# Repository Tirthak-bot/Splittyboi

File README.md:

# Splittyboi
A Split keyboard with low profile switches, Coded with KMK Firmware.

Making this because i want to try a split keeb :3

Using this is pretty straight forward obviously blehh, just connect it to the computer, flash the firmware once and it should just work like a regular keeb moving forward :)

# Schematic
This is the schematic for a single side, both sides are made identically.

# Layout
The layout was designed on https://www.keyboard-layout-editor.com/, The firmware hasn't yet been edited to match this layout and is currently sitting with placeholders.

# PCB
The PCB was designed in Kicad. The matrix wasn't properly aligned to make the look of the PCB More intresting, it will be coded in properly afterwards (Once I make it IRL).

# Case
The case was designed in Fusion. Both sides of the case are based on the same footprint but once it is extruded in the positive axis and once in negetive axis to get a identical case accommodating both right and left sides.

You just drop the pcb in place :) and for the both halfs of the case, they join using magnets!

The magnets are glue and drop, not press fit! So the thin walls around the magnet holes won't cause any problems!

# Firmware
As mentioned above, the firmware is written in python using the KMK Libraries. It will be pushed to the microcontroller using circuit python.

# BOM
|SR.NO|ITEMS|QUANTITY|UNIT PRICE|TOTAL PRICE|URL|
|-----|-----|--------|-----------|-----------|---|
|1|PCB (From JLCPCB)|5 (Minimun)|$10 (Including Shipping)|$50|In my Cart|
|2|Seeed XIAO nRF52840|2 (One for each side)|$12.50 (Including Shipping)|$25|https://robocraze.com/products/seeed-studio-xiao-nrf52840-development-board-supports-bluetooth-5-0|
|3|Gateron LP 2.0 Switches|70|$0.185 (Including Shipping)|$13|https://meckeys.com/shop/accessories/keyboard-accessories/key-switches/gateron-low-profile-2-0-mechanical-switch-3pin/|
|4|Blank DSA Keycaps 1U|70|$0.207 (Including Shipping)|$14.5|https://meckeys.com/shop/accessories/keyboard-accessories/keycaps/blank-dsa-keycaps-1u/|
|5|3.7V LiPo Batteries|2 (One for each side)|$1.615 (Including Shipping)|$3.23|https://quartzcomponents.com/products/3-7v-1000mah-li-po-rechargeable-battery|
|6|1N4148WS T4 Switching Diode|70|$0.025 (Including Shipping)|$1.78|https://quartzcomponents.com/collections/smd-diodes/products/1n4148ws-t4-switching-diode-sod-123-smd-package|
|7|3D Prints|4 Files|idk|idk|Self printed|
|8|Magnets|14|$0|$0|Self sourced|
|Total:|||-|$110||

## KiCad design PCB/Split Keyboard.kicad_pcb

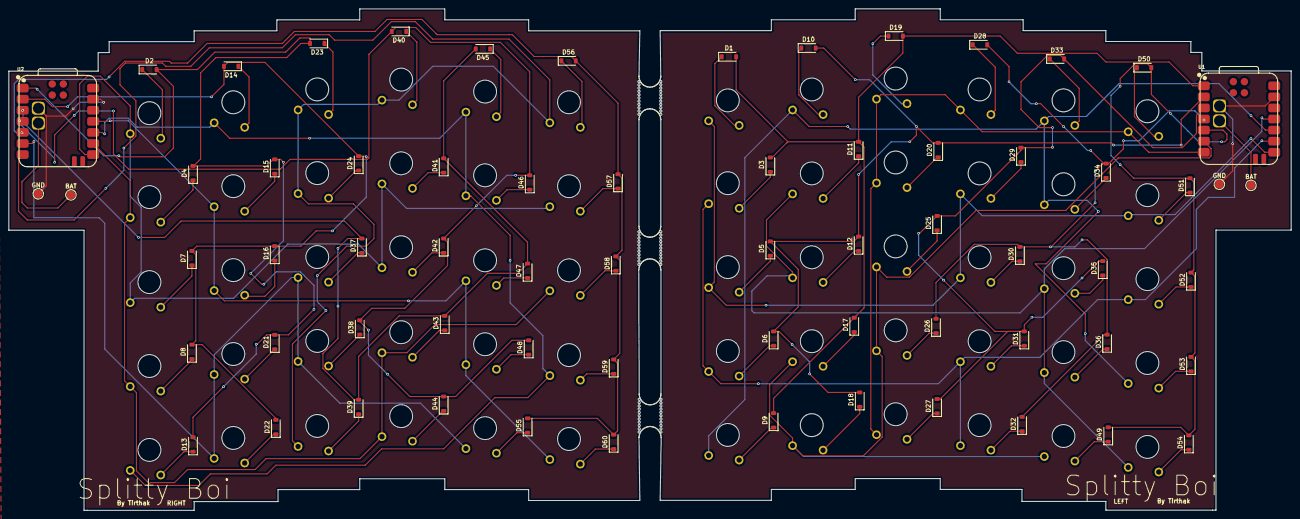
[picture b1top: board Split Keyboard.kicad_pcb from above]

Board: 2 copper layers, 294.2 x 115.0 mm, 129 parts (0 on the bottom side), 74 nets.

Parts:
BAT: BAT; TestPoint_Pad_D2.0mm
BAT#2: BAT; TestPoint_Pad_D2.0mm
D1, D2, D3, D4, D5, D6, D7, D8, D9, D10, D11, D12, D13, D14, D15, D16, D17, D18, D19, D20, D21, D22, D23, D24, D25, D26, D27, D28, D29, D30, D31, D32, D33, D34, D35, D36, D37, D38, D39, D40, D41, D42, D43, D44, D45, D46, D47, D48, D49, D50, D51, D52, D53, D54, D55, D56, D57, D58, D59, D60: D; D_SOD-123
GND: GND; TestPoint_Pad_D2.0mm
GND#2: GND; TestPoint_Pad_D2.0mm
SW1, SW2, SW3, SW4, SW5, SW6, SW7, SW8, SW9, SW10, SW11, SW12, SW13, SW14, SW15, SW16, SW17, SW18, SW19, SW20, SW21, SW22, SW23, SW24, SW25, SW26, SW27, SW28, SW29, SW30, SW31, SW32, SW33, SW34, SW35, SW36, SW37, SW38, SW39, SW40, SW41, SW42, SW43, SW44, SW45, SW46, SW47, SW48, SW49, SW50, SW51, SW52, SW53, SW54, SW55, SW56, SW57, SW58, SW59, SW60: SW_Push; SW_KS33_1u
U1, U2: XIAO-nRF52840-SMD; modified-XIAO-nRF52840-SMD
mouse-bite-5mm-slot, mouse-bite-5mm-slot#2, mouse-bite-5mm-slot#3: VAL**; mouse-bite-5mm-slot

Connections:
COL0: D1.2 (A), D2.2 (A), D3.2 (A), D4.2 (A), D9.2 (A), D11.2 (A), D13.2 (A), D15.2 (A), D17.2 (A), D19.2 (A), D21.2 (A), D23.2 (A), U1.1 (P0.02_A0_D0), U2.1 (P0.02_A0_D0)
COL1: D5.2 (A), D6.2 (A), D7.2 (A), D8.2 (A), D10.2 (A), D12.2 (A), D14.2 (A), D16.2 (A), D18.2 (A), D20.2 (A), D22.2 (A), D24.2 (A), U1.2 (P0.03_A1_D1), U2.2 (P0.03_A1_D1)
COL2: D25.2 (A), D27.2 (A), D29.2 (A), D31.2 (A), D33.2 (A), D35.2 (A), D37.2 (A), D39.2 (A), D41.2 (A), D43.2 (A), D45.2 (A), D47.2 (A), U1.3 (P0.28_A2_D2), U2.3 (P0.28_A2_D2)
COL3: D26.2 (A), D28.2 (A), D30.2 (A), D32.2 (A), D34.2 (A), D36.2 (A), D38.2 (A), D40.2 (A), D42.2 (A), D44.2 (A), D46.2 (A), D48.2 (A), U1.4 (P0.29_A3_D3), U2.4 (P0.29_A3_D3)
COL4: D49.2 (A), D50.2 (A), D51.2 (A), D52.2 (A), D53.2 (A), D54.2 (A), D55.2 (A), D56.2 (A), D57.2 (A), D58.2 (A), D59.2 (A), D60.2 (A), U1.5 (P0.04_A4_D4_SDA), U2.5 (P0.04_A4_D4_SDA)
GND: GND.1, GND#2.1, U1.13 (GND), U1.16 (GND), U2.13 (GND), U2.16 (GND)
unnamed: D1.1 (K), SW1.2
unnamed: D2.1 (K), SW2.2
unnamed: D3.1 (K), SW3.2
unnamed: D4.1 (K), SW4.2
unnamed: D5.1 (K), SW5.2
unnamed: D6.1 (K), SW6.2
unnamed: D7.1 (K), SW7.2
unnamed: D8.1 (K), SW8.2
unnamed: D9.1 (K), SW9.2
unnamed: D10.1 (K), SW10.2
unnamed: D11.1 (K), SW11.2
unnamed: D12.1 (K), SW12.2
unnamed: D13.1 (K), SW13.2
unnamed: D14.1 (K), SW14.2
unnamed: D15.1 (K), SW15.2
unnamed: D16.1 (K), SW16.2
unnamed: D17.1 (K), SW17.2
unnamed: D18.1 (K), SW18.2
unnamed: D19.1 (K), SW19.2
unnamed: D20.1 (K), SW20.2
unnamed: D21.1 (K), SW21.2
unnamed: D22.1 (K), SW22.2
unnamed: D23.1 (K), SW23.2
unnamed: D24.1 (K), SW24.2
unnamed: D25.1 (K), SW25.2
unnamed: D26.1 (K), SW26.2
unnamed: D27.1 (K), SW27.2
unnamed: D28.1 (K), SW28.2
unnamed: D29.1 (K), SW29.2
unnamed: D30.1 (K), SW30.2
unnamed: D31.1 (K), SW31.2
unnamed: D32.1 (K), SW32.2
unnamed: D33.1 (K), SW33.2
unnamed: D34.1 (K), SW34.2
unnamed: D35.1 (K), SW35.2
unnamed: D36.1 (K), SW36.2
unnamed: D37.1 (K), SW37.2
unnamed: D38.1 (K), SW38.2
unnamed: D39.1 (K), SW39.2
unnamed: D40.1 (K), SW40.2
unnamed: D41.1 (K), SW41.2
unnamed: D42.1 (K), SW42.2
unnamed: D43.1 (K), SW43.2
unnamed: D44.1 (K), SW44.2
unnamed: D45.1 (K), SW45.2
unnamed: D46.1 (K), SW46.2
unnamed: D47.1 (K), SW47.2
unnamed: D48.1 (K), SW48.2
unnamed: D49.1 (K), SW49.2
unnamed: D50.1 (K), SW50.2
unnamed: D51.1 (K), SW51.2
unnamed: D52.1 (K), SW52.2
unnamed: D53.1 (K), SW53.2
unnamed: D54.1 (K), SW54.2
unnamed: D55.1 (K), SW55.2
unnamed: D56.1 (K), SW56.2
unnamed: D57.1 (K), SW57.2
unnamed: D58.1 (K), SW58.2
unnamed: D59.1 (K), SW59.2
unnamed: D60.1 (K), SW60.2
unnamed: BAT.1, U1.15 (BAT)
unnamed: BAT#2.1, U2.15 (BAT)
ROW0: SW17.1, SW18.1, SW21.1, SW22.1, SW25.1, SW26.1, SW37.1, SW38.1, SW49.1, SW55.1, U1.6 (P0.05_A5_D5_SCL), U2.6 (P0.05_A5_D5_SCL)
ROW1: SW19.1, SW20.1, SW23.1, SW24.1, SW27.1, SW28.1, SW39.1, SW40.1, SW50.1, SW56.1, U1.7 (P1.11_D6_TX), U2.7 (P1.11_D6_TX)
ROW2: SW1.1, SW2.1, SW5.1, SW7.1, SW29.1, SW30.1, SW41.1, SW42.1, SW51.1, SW57.1, U1.8 (P1.12_D7_RX), U2.8 (P1.12_D7_RX)
ROW3: SW3.1, SW4.1, SW6.1, SW8.1, SW31.1, SW32.1, SW43.1, SW44.1, SW52.1, SW58.1, U1.9 (P1.13_D8_SCK), U2.9 (P1.13_D8_SCK)
ROW4: SW9.1, SW10.1, SW13.1, SW14.1, SW33.1, SW34.1, SW45.1, SW46.1, SW53.1, SW59.1, U1.10 (P1.14_D9_MISO), U2.10 (P1.14_D9_MISO)
ROW5: SW11.1, SW12.1, SW15.1, SW16.1, SW35.1, SW36.1, SW47.1, SW48.1, SW54.1, SW60.1, U1.11 (P1.15_D10_MOSI), U2.11 (P1.15_D10_MOSI)

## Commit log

2025-12-12 README.md
2025-12-12 Create temp
2026-03-21 adding bom.csv file to the repo
